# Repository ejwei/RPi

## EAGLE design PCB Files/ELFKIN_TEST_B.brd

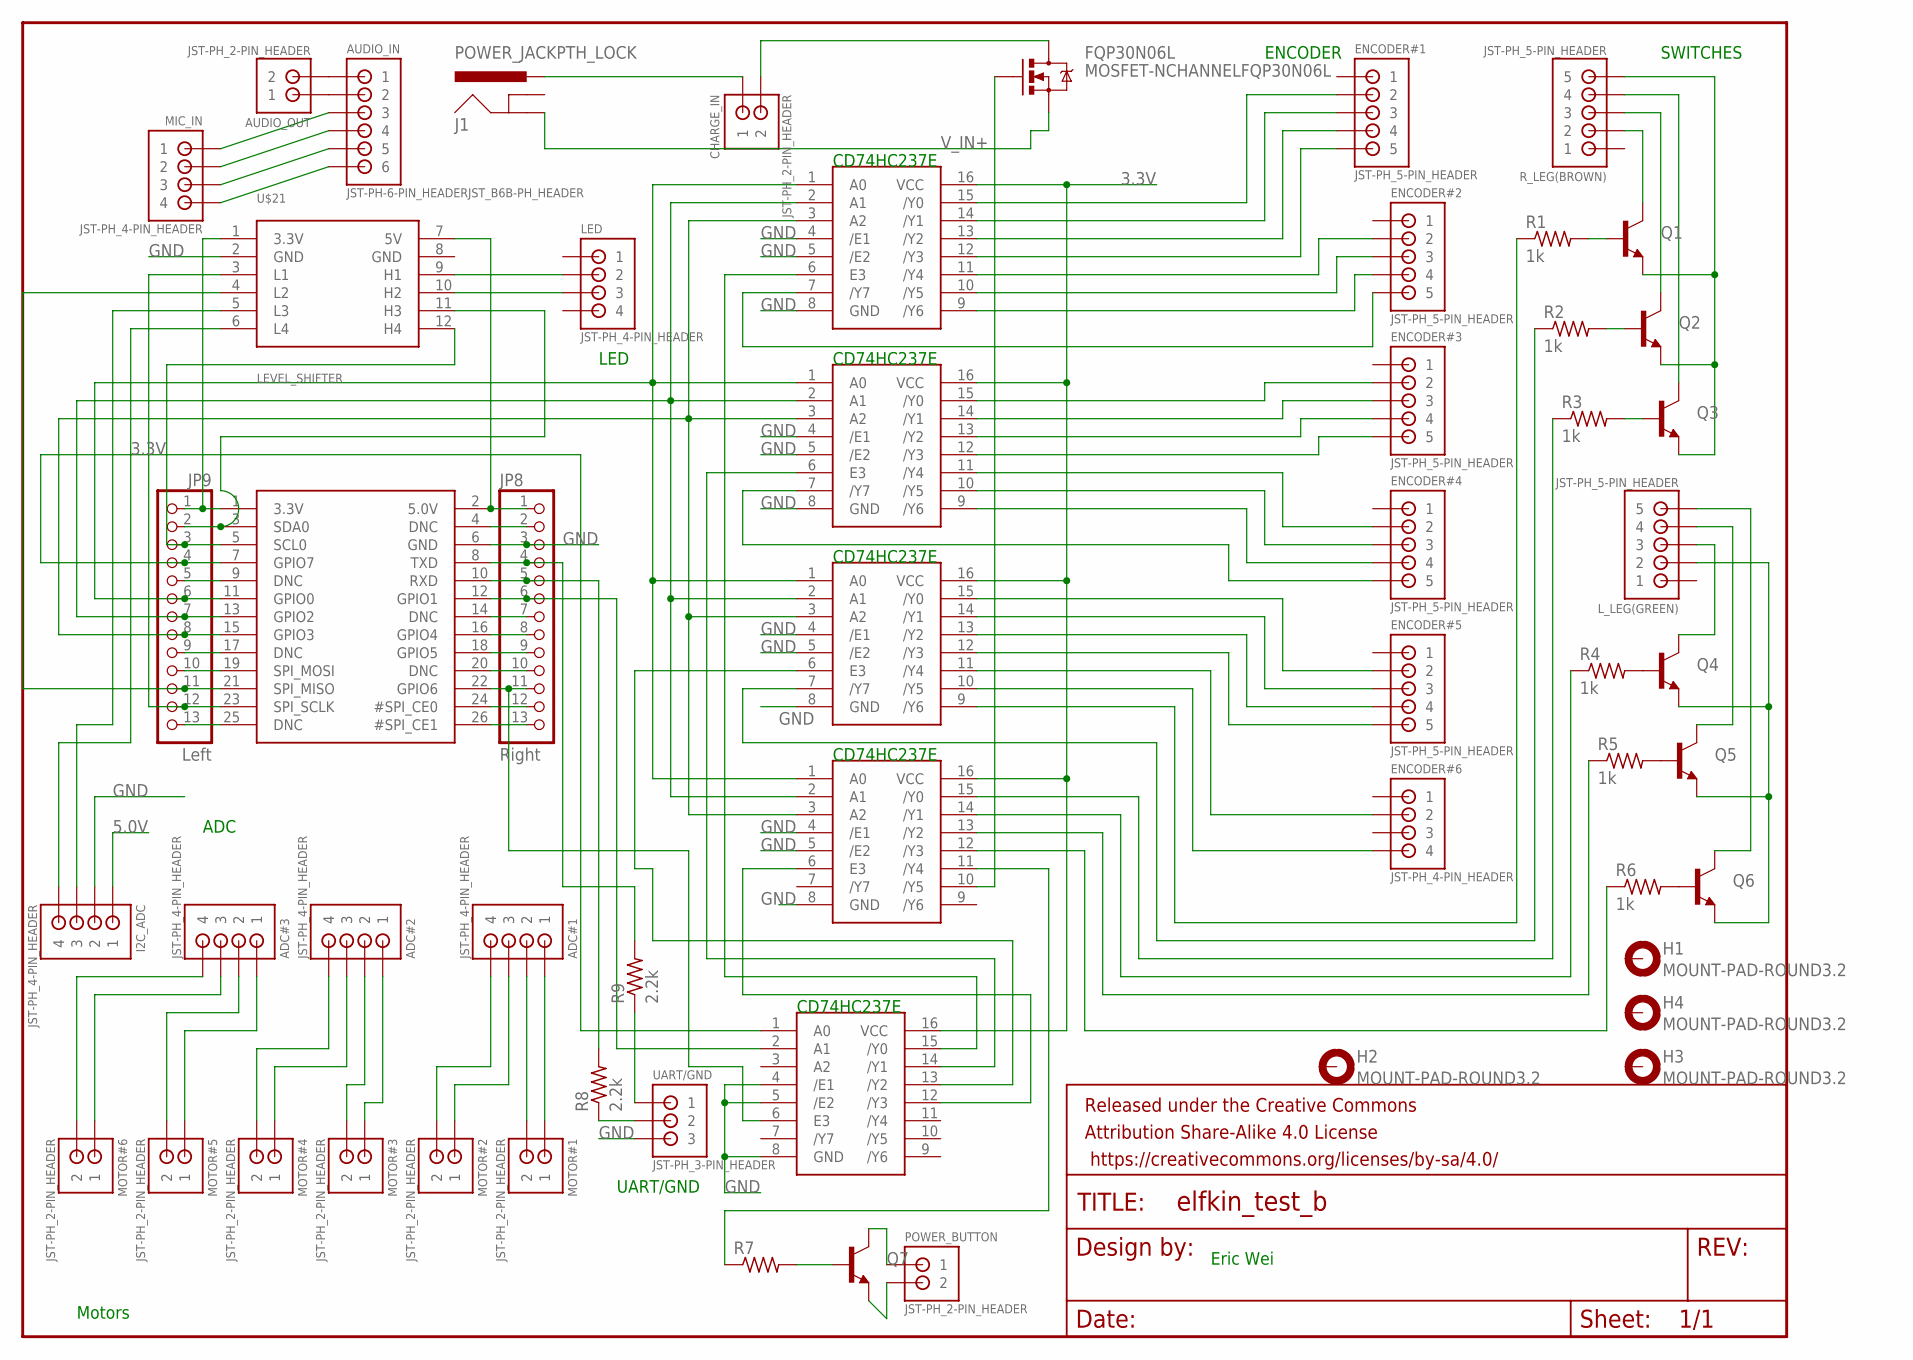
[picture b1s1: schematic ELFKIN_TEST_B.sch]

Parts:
ADC#1, ADC#2, ADC#3: JST-PH_4-PIN_HEADER; JST_B4B-PH_HEADER
AUDIO_IN: JST-PH-6-PIN_HEADERJST_B6B-PH_HEADER; JST_B6B-PH_HEADER
AUDIO_OUT: JST-PH_2-PIN_HEADER; JST_B2B-PH_HEADER
CHARGE_IN: JST-PH_2-PIN_HEADER; JST_B2B-PH_HEADER
ENCODER#1, ENCODER#2, ENCODER#3, ENCODER#4, ENCODER#5: JST-PH_5-PIN_HEADER; JST_B5B-PH_HEADER
ENCODER#6: JST-PH_4-PIN_HEADER; JST_B4B-PH_HEADER
FQP30N06L: MOSFET-NCHANNELFQP30N06L; TO220V
FRAME1: FRAME-LETTER; CREATIVE_COMMONS
H1, H2, H3, H4: MOUNT-PAD-ROUND3.2; 3,2-PAD
I2C_ADC: JST-PH_4-PIN_HEADER; JST_B4B-PH_HEADER
J1: POWER_JACKPTH_LOCK; POWER_JACK_PTH_LOCK
JP7: PI; RASBERRYPI_IDC
JP8: Right; 1X13_ROUND_76MIL
JP9: Left; 1X13_ROUND_76MIL
LED: JST-PH_4-PIN_HEADER; JST_B4B-PH_HEADER
L_LEG(GREEN): JST-PH_5-PIN_HEADER; JST_B5B-PH_HEADER
MIC_IN: JST-PH_4-PIN_HEADER; JST_B4B-PH_HEADER
MOTOR#1, MOTOR#2, MOTOR#3, MOTOR#4, MOTOR#5, MOTOR#6: JST-PH_2-PIN_HEADER; JST_B2B-PH_HEADER
POWER_BUTTON: JST-PH_2-PIN_HEADER; JST_B2B-PH_HEADER
Q1, Q2, Q3, Q4, Q5, Q6, Q7: TRANSISTOR_NPN2N3904; TO-92
R1, R2, R3, R4, R5, R6: 1k; 0207/5V
R7: R-US_0207/5V; 0207/5V
R8, R9: 2.2k; 0207/5V
R_LEG(BROWN): JST-PH_5-PIN_HEADER; JST_B5B-PH_HEADER
U$1, U$2, U$3, U$4, U$5: 74LVC138ADDIL16; DIL16
U$21: LEVEL_SHIFTER
UART/GND: JST-PH_3-PIN_HEADER; JST_B3B-PH_HEADER

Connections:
3.3V: JP7.1 (3.3V), JP9.1, U$1.16 (VCC), U$2.16 (VCC), U$3.16 (VCC), U$4.16 (VCC), U$5.16 (VCC), U$21.1 (3.3V)
5.0V: I2C_ADC.P1 (1), JP7.2 (5.0V), JP8.1, U$21.7 (5V)
GND: I2C_ADC.P2 (2), JP7.6 (GND), JP8.3, U$1.4 (/E1), U$1.5 (/E2), U$1.8 (GND), U$2.4 (/E1), U$2.5 (/E2), U$2.8 (GND), U$3.4 (/E1), U$3.5 (/E2), U$3.8 (GND), U$4.4 (/E1), U$4.5 (/E2), U$4.8 (GND), U$5.4 (/E1), U$5.5 (/E2), U$5.8 (GND), U$21.2 (GND), U$21.8 (GND), UART/GND.P3 (3)
unnamed: JP7.11 (GPIO0), JP9.6, U$1.1 (A0), U$2.1 (A0), U$3.1 (A0), U$4.1 (A0)
unnamed: JP7.13 (GPIO2), JP9.7, U$1.2 (A1), U$2.2 (A1), U$3.2 (A1), U$4.2 (A1)
unnamed: JP7.15 (GPIO3), JP9.8, U$1.3 (A2), U$2.3 (A2), U$3.3 (A2), U$4.3 (A2)
unnamed: ENCODER#1.P2 (2), U$1.15 (/Y0)
unnamed: ENCODER#1.P3 (3), U$1.14 (/Y1)
unnamed: ENCODER#1.P4 (4), U$1.13 (/Y2)
unnamed: ENCODER#1.P5 (5), U$1.12 (/Y3)
unnamed: ENCODER#2.P2 (2), U$1.11 (/Y4)
unnamed: ENCODER#2.P3 (3), U$1.10 (/Y5)
unnamed: ENCODER#2.P4 (4), U$1.9 (/Y6)
unnamed: ENCODER#2.P5 (5), U$1.7 (/Y7)
unnamed: ENCODER#3.P2 (2), U$2.15 (/Y0)
unnamed: ENCODER#3.P3 (3), U$2.14 (/Y1)
unnamed: ENCODER#3.P4 (4), U$2.13 (/Y2)
unnamed: ENCODER#3.P5 (5), U$2.12 (/Y3)
unnamed: ENCODER#4.P2 (2), U$2.11 (/Y4)
unnamed: ENCODER#4.P3 (3), U$2.10 (/Y5)
unnamed: ENCODER#4.P4 (4), U$2.9 (/Y6)
unnamed: ENCODER#4.P5 (5), U$2.7 (/Y7)
unnamed: ENCODER#5.P2 (2), U$3.15 (/Y0)
unnamed: ENCODER#5.P3 (3), U$3.14 (/Y1)
unnamed: ENCODER#5.P4 (4), U$3.13 (/Y2)
unnamed: ENCODER#5.P5 (5), U$3.12 (/Y3)
unnamed: ENCODER#6.P2 (2), U$3.11 (/Y4)
unnamed: ENCODER#6.P4 (4), U$3.10 (/Y5)
unnamed: R2.1, U$3.7 (/Y7)
unnamed: ADC#1.P1 (1), MOTOR#1.P1 (1)
unnamed: ADC#1.P2 (2), MOTOR#1.P2 (2)
unnamed: ADC#1.P3 (3), MOTOR#2.P1 (1)
unnamed: ADC#1.P4 (4), MOTOR#2.P2 (2)
unnamed: ADC#2.P1 (1), MOTOR#3.P1 (1)
unnamed: ADC#2.P2 (2), MOTOR#3.P2 (2)
unnamed: ADC#2.P3 (3), MOTOR#4.P1 (1)
unnamed: ADC#2.P4 (4), MOTOR#4.P2 (2)
unnamed: ADC#3.P1 (1), MOTOR#5.P1 (1)
unnamed: ADC#3.P2 (2), MOTOR#5.P2 (2)
unnamed: ADC#3.P3 (3), MOTOR#6.P1 (1)
unnamed: ADC#3.P4 (4), MOTOR#6.P2 (2)
unnamed: Q1.2 (B), R1.2
unnamed: Q3.2 (B), R3.2
unnamed: Q2.2 (B), R2.2
unnamed: Q4.2 (B), R4.2
unnamed: Q5.2 (B), R5.2
unnamed: Q6.2 (B), R6.2
unnamed: R1.1, U$3.9 (/Y6)
unnamed: R3.1, U$4.15 (/Y0)
unnamed: R4.1, U$4.14 (/Y1)
unnamed: R5.1, U$4.13 (/Y2)
unnamed: Q1.1 (E), Q2.1 (E), Q3.1 (E), R_LEG(BROWN).P5 (5)
unnamed: R6.1, U$4.12 (/Y3)
unnamed: AUDIO_IN.P3 (3), MIC_IN.P1 (1)
unnamed: I2C_ADC.P4 (4), U$21.6 (L4)
unnamed: JP7.7 (GPIO7), JP9.4, U$5.1 (A0)
unnamed: JP7.9 (DNC), JP9.5
unnamed: L_LEG(GREEN).P2 (2), Q4.1 (E), Q5.1 (E), Q6.1 (E)
unnamed: L_LEG(GREEN).P3 (3), Q4.3 (C)
unnamed: Q1.3 (C), R_LEG(BROWN).P2 (2)
unnamed: JP7.17 (DNC), JP9.9
unnamed: JP7.19 (SPI_MOSI), JP9.10
unnamed: JP7.18 (GPIO5), JP8.9
unnamed: JP7.23 (SPI_SCLK), JP9.12, U$21.3 (L1)
unnamed: JP7.25 (DNC), JP9.13
unnamed: JP7.4 (DNC), JP8.2
unnamed: Q2.3 (C), R_LEG(BROWN).P3 (3)
unnamed: JP7.10 (RXD), JP8.5, R8.2
unnamed: JP7.12 (GPIO1), JP8.6, U$5.2 (A1)
unnamed: JP7.14 (DNC), JP8.7
unnamed: JP7.16 (GPIO4), JP8.8
unnamed: JP7.20 (DNC), JP8.10
unnamed: JP7.22 (GPIO6), JP8.11, U$5.6 (E3)
unnamed: JP7.24 (#SPI_CE0), JP8.12
unnamed: JP7.26 (#SPI_CE1), JP8.13
unnamed: L_LEG(GREEN).P4 (4), Q5.3 (C)
unnamed: L_LEG(GREEN).P5 (5), Q6.3 (C)
unnamed: I2C_ADC.P3 (3), U$21.5 (L3)
unnamed: AUDIO_IN.P4 (4), MIC_IN.P2 (2)
unnamed: Q7.2 (B), R7.2
unnamed: POWER_BUTTON.P1 (1), Q7.3 (C)
unnamed: POWER_BUTTON.P2 (2), Q7.1 (E)
unnamed: R7.1, U$4.11 (/Y4)
unnamed: CHARGE_IN.P1 (1), J1.PWR
unnamed: FQP30N06L.1 (G), U$4.10 (/Y5)
unnamed: AUDIO_IN.P2 (2), AUDIO_OUT.P1 (1)
unnamed: AUDIO_IN.P1 (1), AUDIO_OUT.P2 (2)
unnamed: U$1.6 (E3), U$5.15 (/Y0)
unnamed: U$2.6 (E3), U$5.14 (/Y1)
unnamed: U$3.6 (E3), U$5.13 (/Y2)
unnamed: Q3.3 (C), R_LEG(BROWN).P4 (4)
unnamed: U$4.6 (E3), U$5.12 (/Y3)
unnamed: JP7.8 (TXD), JP8.4, R9.2
unnamed: AUDIO_IN.P5 (5), MIC_IN.P3 (3)
unnamed: AUDIO_IN.P6 (6), MIC_IN.P4 (4)
unnamed: LED.P2 (2), U$21.9 (H1)
unnamed: LED.P3 (3), U$21.10 (H2)
unnamed: R8.1, UART/GND.P2 (2)
unnamed: R9.1, UART/GND.P1 (1)
unnamed: CHARGE_IN.P2 (2), FQP30N06L.2 (D)
unnamed: JP7.21 (SPI_MISO), JP9.11, U$21.4 (L2)
unnamed: JP7.5 (SCL0), JP9.3, U$21.12 (H4)
unnamed: JP7.3 (SDA0), JP9.2, U$21.11 (H3)
V_IN+: FQP30N06L.3 (S), J1.GND

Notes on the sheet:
SWITCHES
ENCODER
LED
Motors
UART/GND
ADC
Eric Wei
CD74HC237E

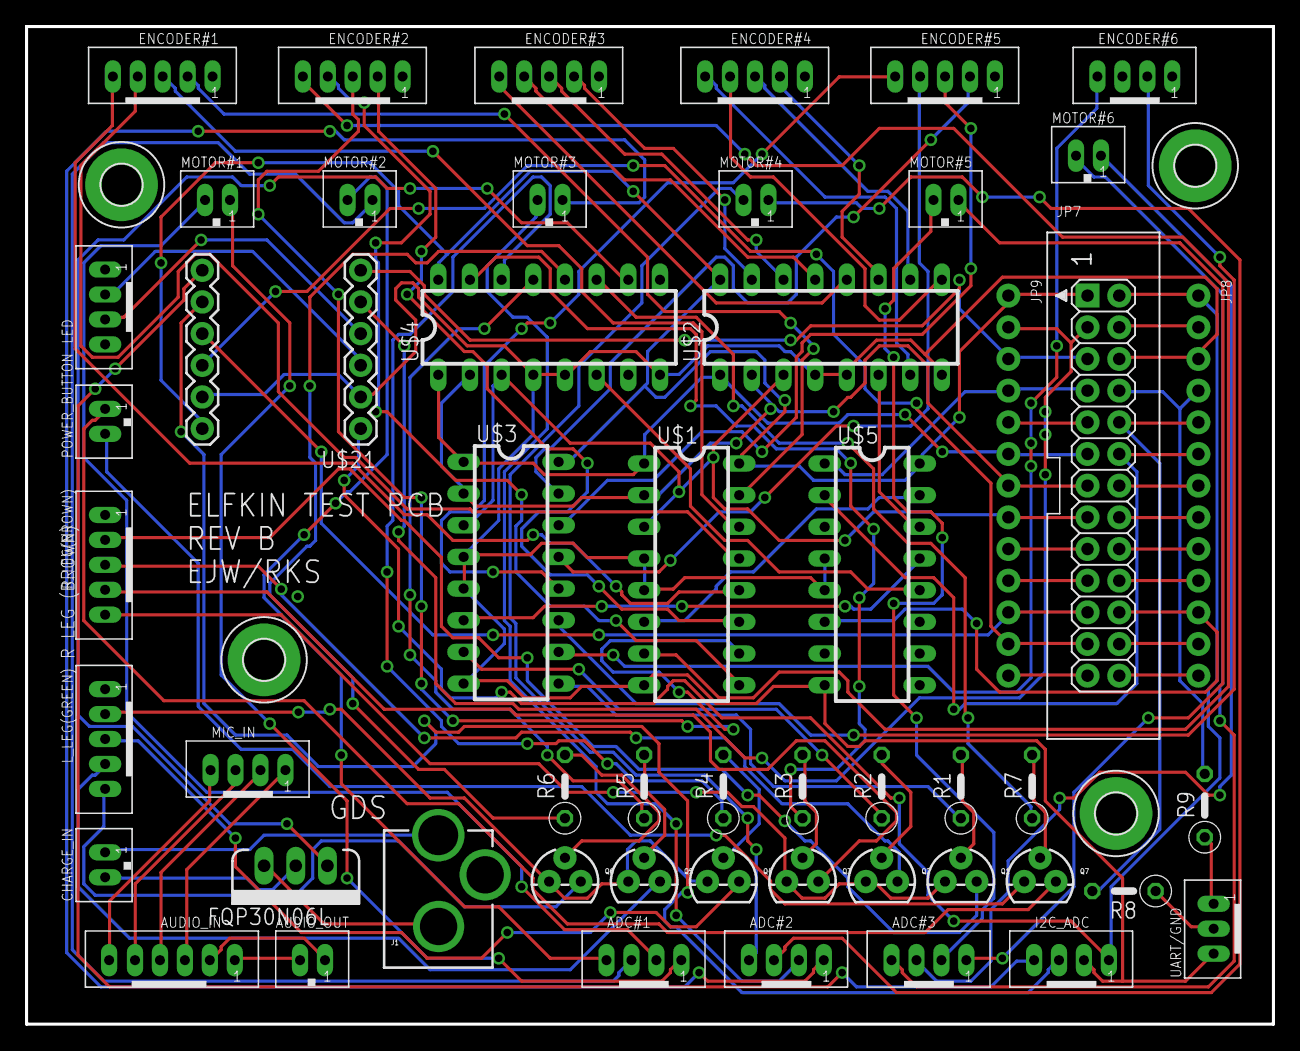
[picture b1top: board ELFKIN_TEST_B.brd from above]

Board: 2 copper layers, 100.0 x 80.0 mm, 57 parts (0 on the bottom side), 104 nets.

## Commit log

2016-10-24 Inital Commit
2016-10-24 Added 3rd State
2016-10-24 Add Serial Test
2016-10-24 update serial module
2016-10-24 import serial from PySerial
2016-10-24 Added Serial to demux_test
2016-10-24 Added : to Loops
2016-10-24 changed to port
2016-10-24 Changed Initial State
2016-10-24 Fixed Output
2016-10-24 play with the timeout
2016-10-24 Play with printing inwaiting
2016-10-24 Printing out of loop
2016-10-25 Update to Wait for Bytes and to Print Test Completed
2016-10-25 Add Breakpoints
2016-10-25 Remove Breakpoints
2016-10-25 Added multiple threads
2016-10-25 corrected caps on readline
2016-10-25 thread fix
2016-10-25 change to read
2016-10-25 removed extra thread starts
2016-10-25 testcomplete case
2016-10-25 setTimeout
2016-10-25 Increase Time
2016-10-25 timeout to 5
2016-10-25 read 1 byte at a time
2016-10-25 timeout = None
2016-10-25 debug print
2016-10-25 Error Fixed
2016-10-25 debug
2016-10-25 Remove Time Statements
2016-10-25 Move Port Close to Print Thread
2016-10-25 close the thread when done
2016-10-25 Port Closing Debug
2016-10-25 && replaced with and
2016-10-25 Pass TestComplete by Reference
2016-10-25 Moved thread 2 definition
2016-10-25 changed argument definition to tuple
2016-10-25 Change thread start
2016-10-25 added extra delay
2016-10-25 PortWaiting to only block if there is something to read
2016-10-25 update to inwaiting
2016-10-25 TestComplete Check
2016-10-25 change to bytesToRead
2016-10-25 change testComplete to a global
2016-10-25 added break
2016-10-25 added Byte checks
2016-10-25 Join The Threads
2016-10-25 reduce time
2016-10-25 Added Thread 2 tracker
2016-10-25 Removed White Space
2016-10-25 print test Complete
2016-10-25 Turned into Classes
2016-10-25 Update Indent
2016-10-25 corrected inits
2016-10-25 Queue Revision
2016-10-25 revise Thread Call
2016-10-25 update thread.start()
2016-11-03 Update to test test board
2016-11-03 Removed A2 Dependency
2016-11-03 Update BCM Numbering
2016-11-04 Add extra pins to test
2016-11-04 change up gpio outputs
2016-11-04 Update BCM numbers
2016-11-04 Full truth table
2016-11-04 Fix demux out of Y6
2016-11-04 Added mux for all lines
2016-11-21 added extra time to wait
2016-11-21 initial
2016-11-21 Update Charger to Y5
2016-12-01 added recording
2016-12-01 mono recording
2016-12-01 mono recording louder
2016-12-01 mono recording medium
2016-12-01 Add Truth Tablet and FFT Test
2016-12-02 read line added
2016-12-02 revert
2016-12-02 retry Read Line
2016-12-02 add serial write test
2016-12-02 added "
2016-12-02 add flush
2016-12-02 changed serial test
2016-12-02 \r\n
2016-12-02 led test
2016-12-08 Initial infrastructure to run all tests from a central location
2016-12-08 move function list definition
2016-12-08 remove self argument for functions not in classes
2016-12-08 some cleanup on the RPI side
2016-12-08 cleanup print thread, don't start it multiple times either
2016-12-08 whitespace error
2016-12-08 cleanup print statements, add some delays to charge test
2016-12-08 only setup GPIOs once
2016-12-08 clean up GPIOs before initialization
2016-12-08 update network info to use tplink router
2016-12-08 Added truth Table comments
2016-12-09 now has first rev of gpio on/off stuff
2016-12-09 working FCT ubuntu script - everything but encoders
2016-12-09 truth table had A0 and A2 reversed
2016-12-09 add better print messages
2016-12-09 encoder test uses motor spin mode
2016-12-09 some more prints to help debug button error
2016-12-10 add the full suite of tests in order
2016-12-10 Bug in test list
2016-12-14 Added PCB Files
2017-01-04 Working button tests (no command automation) with the FCT Test Board v2.
2017-01-05 Working button & encoder testing, and working bring up code for the numato gpio extender
2017-01-05 script builds. Infrastructure in place for using numato controller. Power button implemented as an example.
2017-01-05 power button, toe buttons, and power mosfet automation all working with the numato gpio controller
2017-01-05 working encoder test
2017-01-06 Fully working fct desktop tester

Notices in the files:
parts and their libraries:
SparkFun-Aesthetics: Licensing: Creative Commons ShareAlike 4.0 International - https://creativecommons.org/licenses/by-sa/4.0
SparkFun-Aesthetics: Released under the Creative Commons Attribution Share-Alike 4.0 License
SparkFun-Aesthetics: https://creativecommons.org/licenses/by-sa/4.0
